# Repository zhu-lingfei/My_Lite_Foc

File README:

# 基于DRV8313的FOC驱动器

## 描述

本驱动板适用于4008/4010云台无刷电机，使用不高于16V电压。主控采用STM32F103C8T6,驱动芯片为DRV8313/AT8313，最大电流2.5A，使用低侧电流采样，驱动板集成CAN收发器，使用CAN通讯控制。

<div align="center">
    
</div>

项目参考自[B站UP主：会飞的车_S](https://www.bilibili.com/video/BV1nv4y1G73a/?spm_id_from=333.999.0.0&amp;vd_source=1aaa4eb0748d3bced4e39449a442883b)的开源项目，在硬件上做出如下修改：

1. 修改原本的母线电流采样为低侧电流采样，母线电流采样对运放要求较高，需要使用比常规放大器更好的PWM抑制功能的高精度双向运放，原设计采用INA240,价格比较高；低侧采样则对运放没什么要求，这里使用INA181。
   
   <div align="center">
    
   </div>
   <div align="center">

   </div>

2. 运放参考电压使用电阻分压加电压跟随器，降低阻抗。参考电压为1.65v，满足双向电流采样的电压偏置。可使用OPA333或OPA348，OPA348价格比较低。
   
   <div align="center">
    
   </div>

由于原本是画在一块方板子上的，后来改了圆板子，很多布局是直接复制过来的，也懒得修改了，看起来有些奇怪，但是能跑就行。
运放可以只焊接两个，即U相和V相，W相（红框内）可不焊接。

<div align="center">
    
</div>

## 程序

固件修改自[B站UP主：会飞的车_S](https://space.bilibili.com/342241148?spm_id_from=333.788.0.0)及群主：小时候可吊了。修改的内容如下：

1. 将原本定时器更新中断中使用软件触发电流采样修改为定时器通道4输出OC4REF触发AD采样，使用ADC1和ADC2注入组分别采集U相和V相的电流，使用规则组采集电源电压。
2. 添加CAN控制指令
3. 添加FreeRtos
   [GIT仓库地址](https://github.com/zhu-lingfei/My_Lite_Foc)（还未提交最终版本，修改ing）

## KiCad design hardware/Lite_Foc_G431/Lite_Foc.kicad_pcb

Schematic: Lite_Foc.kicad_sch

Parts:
C1, C2, C3, C4, C30, C31, C32, C33: 100nf; C_0603_1608Metric
C5: 0.1u; C_1206_3216Metric
C6: 320uf; CP_Elec_8x10
C7, C22: 0.1u; C_0603_1608Metric
C8, C26: 0.01u; C_0603_1608Metric
C9: 4.7uF; R_0603_1608Metric
C10, C14: 104; C_0603_1608Metric
C11: 10uF; R_0603_1608Metric
C12, C13: 1uF; C_0603_1608Metric
C15: 22uF; C_0805_2012Metric
C16, C18: 10uF; C_0603_1608Metric
C17, C20, C21: C; C_0603_1608Metric
C19, C23, C24, C25, C29: 0.1uF; C_0603_1608Metric
CN1: XT30PW-M; CONN-TH_XT30PW-M
CN2: GH1.25-2PWBPZ; CONN-SMD_GH1.25-2PWBPZ
CN3: MR30PW-F; MR30-M
D1: 1N4148WS; D_SOD-323
D4: SMAJ30CA; SMA_L4.4-W2.6-LS5.0-BI
D5: SS34; SMA_L4.3-W2.6-LS5.2-RD
D6, D7, D8, D9, D10, D11, D12, D13, D14: 1N4148WT; D_SOD-523
FPC1: KH-FG0.5-H2.0-13PIN; FPC-SMD_13P-P0.50_KINGHELM_KH-FG0.5-H2.0-13PIN
H1, H2, H3, H4: MountingHole_Pad; MountingHole_2.2mm_M2_DIN965_Pad_TopBottom
IC1: JW5026; SOT-23-6
IC2: ME6211C33M5G-N; SOT-23-5
J1: USB_C_Receptacle_USB2.0; USB_C_Receptacle_G-Switch_GT-USB-7010ASV
L1: 4.7uH; L_Changjiang_FNR4010S
L2: 15uH; L_6.3x6.3_H3
L3, L4: 0R100M; L_0603_1608Metric
Q1, Q2, Q3, Q4, Q5, Q6: AON7544
R1, R2, R3, R4, R5, R6: 2.2R; R_0603_1608Metric
R7, R8, R9: 0.01R; R_1206_3216Metric
R10, R11, R15, R16, R24: 10k; R_0603_1608Metric
R12, R28, R29, R32: R; R_0603_1608Metric
R13: 0R; R_0603_1608Metric
R14: 120R; R_0603_1608Metric
R22: 3.3R; R_0603_1608Metric
R23: 100k; R_0603_1608Metric
R25: 100K; R_0603_1608Metric
R26: 2.1K; R_0603_1608Metric
R27: 11.2K; R_0603_1608Metric
R30: 150k; R_0603_1608Metric
SW1: 按键开关-2P-3*5*2; 贴片按键-2P-3_5_2
U1: FD6288Q; QFN50P400X400X90-25N
U2: STM32G431C8Tx; LQFP-48_7x7mm_P0.5mm
U3: CH9102F; QFN-24-1EP_4x4mm_P0.5mm_EP2.6x2.6mm
U4: MP1584EN; SOIC-8_L4.9-W3.9-P1.27-LS6.0-BL-EP3.3
U5, U6, U7: INA181; SOT-23-6
U8: GH1.25-5PWBPZ; CONN-SMD_5P-P1.25_GH1.25-5PWBPZ
U9: MAX3051; SOT-23-8_L3.0-W1.7-P0.65-LS2.8-TL
Y1: Crystal_GND3; CRYSTAL-SMD_3P-L3.2-W1.3-P1.2-L

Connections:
+5V: C11.2, C12.2, C22.1, C32.2, D1.1 (K), IC2.1 (VIN), IC2.3 (CE), L1.2, R27.1, U3.7 (VDD5), U3.8 (VBUS), U9.3 (VDD)
+12V: C4.2, C9.2, C15.2, C16.2, C29.2, D12.2 (A), D13.2 (A), D14.2 (A), IC1.5 (VIN), L2.1, R25.2, R28.1, U1.4 (VCC)
/CANH: CN2.2, R14.1, U9.7 (CANH)
/CANL: CN2.1, R14.2, U9.6 (CANL)
/FDCAN_RX: U2.33 (PA11), U9.4 (RXD)
/FDCAN_TX: U2.34 (PA12), U9.1 (TXD)
/GHA: D6.1 (K), R1.1, U1.19 (HO1)
/GHB: D9.1 (K), R3.1, U1.16 (HO2)
/GHC: D11.1 (K), R5.1, U1.13 (HO3)
/GLA: D7.1 (K), R2.1, U1.11 (LO1)
/GLB: D8.1 (K), R4.1, U1.10 (LO2)
/GLC: D10.1 (K), R6.1, U1.9 (LO3)
/KEY1: R15.1, U2.39 (PA15)
/KEY2: R16.1, U2.46 (PB9)
/OSC_IN: U2.5 (PF0), Y1.1
/OSC_OUT: U2.6 (PF1), Y1.2
/SHA: C1.2, CN3.3, Q1.1 (S), Q2.3 (D), U1.18 (VS1)
/SHB: C2.2, CN3.2, Q3.1 (S), Q4.3 (D), U1.15 (VS2)
/SHC: C3.2, CN3.1, Q5.1 (S), Q6.3 (D), U1.12 (VS3)
/SPA: Q2.1 (S), R7.1, U5.3 (+)
/SPB: Q4.1 (S), R8.1, U6.3 (+)
/SPC: Q6.1 (S), R9.1, U7.3 (+)
/SPI1_MISO: U2.41 (PB4), U8.3
/SPI1_MOSI: U2.42 (PB5), U8.4
/SPI1_SCK: U2.40 (PB3), U8.2
/SWCLK: FPC1.4, U2.38 (PA14)
/SWDIO: FPC1.8, U2.37 (PA13)
/TIM1CH1: U1.22 (HIN1), U2.30 (PA8)
/TIM1CH1N: U1.1 (LIN1), U2.27 (PB13)
/TIM1CH2: U1.23 (HIN2), U2.31 (PA9)
/TIM1CH2N: U1.2 (LIN2), U2.28 (PB14)
/TIM1CH3: U1.24 (HIN3), U2.32 (PA10)
/TIM1CH3N: U1.3 (LIN3), U2.29 (PB15)
/TIM4_CH1: FPC1.1, U2.43 (PB6)
/TIM4_CH2: FPC1.2, U2.44 (PB7)
/TIM4_CH3: FPC1.3, U2.45 (PB8)
/UART1_RX: U2.25 (PB11), U3.21 (TXD)
/UART1_TX: U2.22 (PB10), U3.20 (RXD)
/USB_DN: J1.A7 (D-), J1.B7 (D-), U3.4 (D-)
/USB_DP: J1.A6 (D+), J1.B6 (D+), U3.3 (D+)
AVDD: C23.1, C24.1, C25.1, C30.2, L3.2, R10.1, U2.20 (VREF+), U2.21 (VDDA), U5.6 (V+), U6.6 (V+), U7.6 (V+)
GND: C4.1, C7.2, C9.1, C11.1, C12.1, C13.1, C14.1, C15.1, C16.1, C18.2, C19.2, C20.2, C21.2, C22.2, C23.2, C24.2, C25.2, C26.1, C29.1, C31.1, C32.1, C33.2, CN2.3, CN2.4, D5.2 (A), FPC1.13, H1.1, H2.1, H3.1, H4.1, IC1.2 (GND), IC2.2 (VSS), J1.A1 (GND), J1.A12 (GND), J1.B1 (GND), J1.B12 (GND), J1.S1 (SHIELD), L4.1, R11.2, R13.2, R24.2, R26.1, R29.2, R30.2, SW1.1, U1.6 (COM), U1.25 (EXP), U2.23 (VSS), U2.35 (VSS), U2.47 (VSS), U3.2 (GND), U3.25 (GND), U4.5 (GND), U4.9 (GND), U5.2 (GND), U6.2 (GND), U7.2 (GND), U9.2 (GND), U9.8 (RS), Y1.3
GNDA: C30.1, L4.2, U2.19 (VSSA)
GNDPWR: C5.2, C6.2, C8.2, CN1.1, D4.2 (A), R7.2, R8.2, R9.2, R13.1, U5.4 (-), U6.4 (-), U7.4 (-)
ISA: U2.8 (PA0), U5.1
ISB: U2.9 (PA1), U6.1
ISC: U2.10 (PA2), U7.1
unnamed: C8.1, R22.2
unnamed: C20.1, R12.2
unnamed: D1.2 (A), J1.A4 (VBUS), J1.A9 (VBUS), J1.B4 (VBUS), J1.B9 (VBUS)
unnamed: C17.1, D5.1 (K), L2.2, U4.1 (SW)
unnamed: D6.2 (A), Q1.2 (G), R1.2
unnamed: D7.2 (A), Q2.2 (G), R2.2
unnamed: D8.2 (A), Q4.2 (G), R4.2
unnamed: D9.2 (A), Q3.2 (G), R3.2
unnamed: D10.2 (A), Q6.2 (G), R6.2
unnamed: D11.2 (A), Q5.2 (G), R5.2
unnamed: C1.1, D12.1 (K), U1.20 (VB1)
unnamed: C2.1, D13.1 (K), U1.17 (VB2)
unnamed: C3.1, D14.1 (K), U1.14 (VB3)
unnamed: FPC1.10, R15.2
unnamed: FPC1.11, R16.2
unnamed: C10.1, IC1.1 (BST)
unnamed: IC1.4 (EN), R25.1
unnamed: IC1.3 (FB), R26.2, R27.2
unnamed: C10.2, IC1.6 (SW), L1.1
unnamed: C26.2, SW1.2, U2.7 (PG10)
unnamed: C33.1, U3.5 (VIO), U3.6 (V3)
unnamed: C17.2, U4.8 (BST)
unnamed: C21.1, R12.1, U4.3 (COMP)
unnamed: R32.1, U4.2 (EN)
unnamed: R28.2, R29.1, U4.4 (FB)
unnamed: R30.1, U4.6 (FREQ)
UDC: U2.11 (PA3)
Udc: C7.1, R23.2, R24.1
VBUS: C5.1, C6.1, C18.1, C19.1, CN1.2, D4.1 (K), Q1.3 (D), Q3.3 (D), Q5.3 (D), R22.1, R23.1, R32.2, U4.7 (VIN)
VCC_3V3: C13.2, C14.2, C31.2, FPC1.12, IC2.5 (VOUT), L3.1, U2.1 (VBAT), U2.24 (VDD), U2.36 (VDD), U2.48 (VDD)
VREF: R10.2, R11.1, U5.5 (REF), U6.5 (REF), U7.5 (REF)

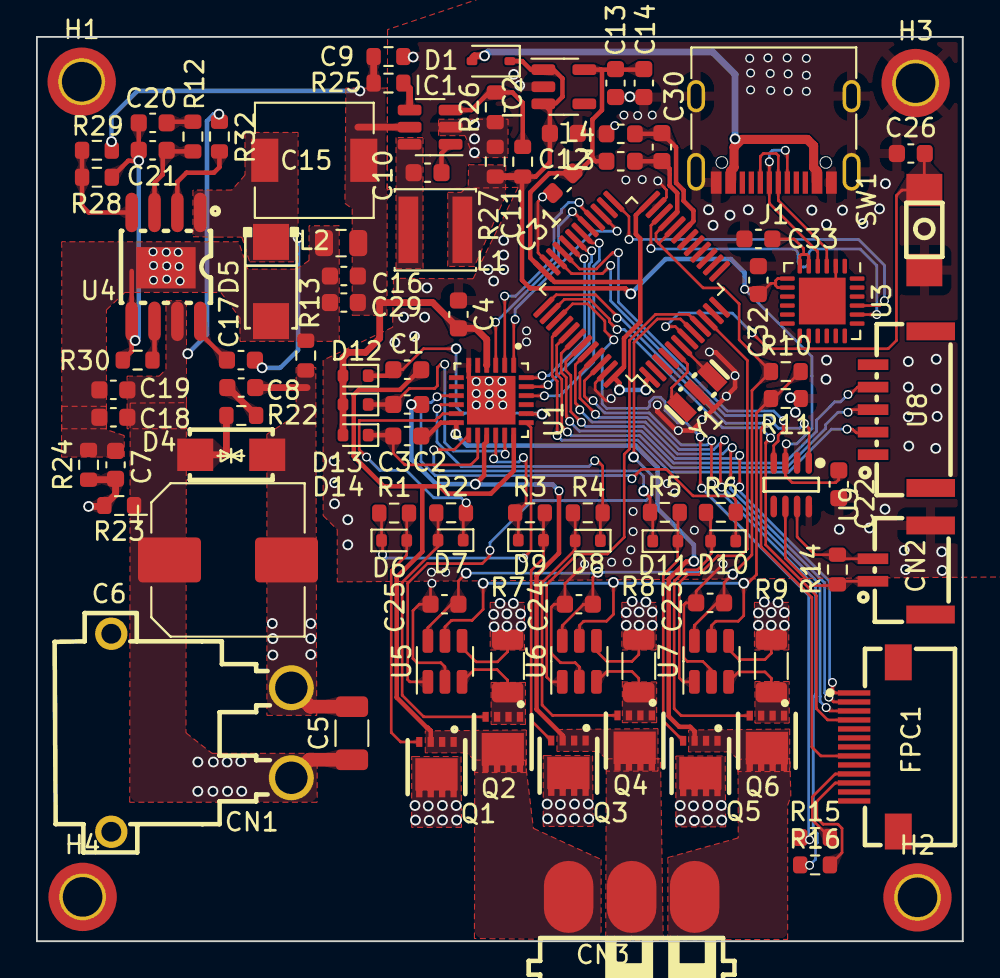
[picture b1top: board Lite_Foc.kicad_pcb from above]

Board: 2 copper layers, 51.4 x 50.2 mm, 101 parts (0 on the bottom side), 77 nets.

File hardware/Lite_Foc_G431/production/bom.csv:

Designator,Footprint,Quantity,Value,LCSC Part #
"C1, C2, C3, C30, C31, C32, C33, C4",0603,8,100nf,
"C10, C14",0603,2,104,
"C11, C16, C18",0603,3,10uF,
"C12, C13",0603,2,1uF,
C15,0805,1,22uF,
"C17, C20, C21",0603,3,C,
"C19, C23, C24, C25, C29",0603,5,0.1uF,
"C22, C7",0603,2,0.1u,
"C26, C8",0603,2,0.01u,
C5,1206,1,0.1u,
C6,CP_Elec_8x10,1,320uf,
C9,0603,1,4.7uF,
CN1,CONN-TH_XT30PW-M,1,XT30PW-M,
CN2,CONN-SMD_GH1.25-2PWBPZ,1,GH1.25-2PWBPZ,
CN3,MR30-M,1,MR30PW-F,
D1,D_SOD-323,1,1N4148WS,
"D10, D11, D12, D13, D14, D6, D7, D8, D9",D_SOD-523,9,1N4148WT,
D4,SMA_L4.4-W2.6-LS5.0-BI,1,SMAJ30CA,
D5,SMA_L4.3-W2.6-LS5.2-RD,1,SS34,
FPC1,FPC-SMD_13P-P0.50_KINGHELM_KH-FG0.5-H2.0-13PIN,1,KH-FG0.5-H2.0-13PIN,
"H1, H2, H3, H4",MountingHole_2.2mm_M2_DIN965_Pad_TopBottom,4,MountingHole_Pad,
IC1,SOT-23-6,1,JW5026,
IC2,SOT-23-5,1,ME6211C33M5G-N,
J1,USB_C_Receptacle_G-Switch_GT-USB-7010ASV,1,USB_C_Receptacle_USB2.0,
L1,L_Changjiang_FNR4010S,1,4.7uH,
L2,L_6.3x6.3_H3,1,15uH,
"L3, L4",0603,2,0R100M,
"Q1, Q2, Q3, Q4, Q5, Q6",AON7544,6,AON7544,
"R1, R2, R3, R4, R5, R6",0603,6,2.2R,
"R10, R11, R15, R16, R24",0603,5,10k,
"R12, R28, R29, R32",0603,4,R,
R13,0603,1,0R,
R14,0603,1,120R,
R22,0603,1,3.3R,
"R23, R25",0603,2,100k,
R26,0603,1,2.1K,
R27,0603,1,11.2K,
R30,0603,1,150k,
"R7, R8, R9",1206,3,0.01R,
SW1,贴片按键-2P-3_5_2,1,按键开关-2P-3*5*2,
U1,QFN50P400X400X90-25N,1,FD6288Q,
U2,LQFP-48_7x7mm_P0.5mm,1,STM32G431C8Tx,
U3,QFN-24-1EP_4x4mm_P0.5mm_EP2.6x2.6mm,1,CH9102F,
U4,SOIC-8_L4.9-W3.9-P1.27-LS6.0-BL-EP3.3,1,MP1584EN,
"U5, U6, U7",SOT-23-6,3,INA181,
U8,CONN-SMD_5P-P1.25_GH1.25-5PWBPZ,1,GH1.25-5PWBPZ,
U9,SOT-23-8_L3.0-W1.7-P0.65-LS2.8-TL,1,MAX3051,
Y1,CRYSTAL-SMD_3P-L3.2-W1.3-P1.2-L,1,Crystal_GND3,

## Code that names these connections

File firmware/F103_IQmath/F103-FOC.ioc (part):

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Mcu.Name=STM32F103C(8-B)Tx
Mcu.Package=LQFP48
Mcu.UserName=STM32F103C8Tx
PA0-WKUP.Signal=ADCx_IN0
PA10.Signal=S_TIM1_CH3
PA11.Mode=CAN_Activate
PA11.Signal=CAN_RX
PA12.Mode=CAN_Activate
PA12.Signal=CAN_TX
PA13.Mode=JTAG_5_pins
PA13.Signal=SYS_JTMS-SWDIO
PA14.Mode=JTAG_5_pins
PA14.Signal=SYS_JTCK-SWCLK
PA15.Mode=JTAG_5_pins
PA15.Signal=SYS_JTDI
PA2.Signal=ADCx_IN2
PA3.Signal=ADCx_IN3
PA4.GPIOParameters=GPIO_Speed,PinState,GPIO_Label
PA4.GPIO_Label=nRESET
PA4.GPIO_Speed=GPIO_SPEED_FREQ_LOW
PA4.PinState=GPIO_PIN_SET
PA4.Signal=GPIO_Output
PA5.Mode=Full_Duplex_Master
PA5.Signal=SPI1_SCK
PA6.Mode=Full_Duplex_Master
PA6.Signal=SPI1_MISO
PA7.Mode=Full_Duplex_Master
PA7.Signal=SPI1_MOSI
PA8.Signal=S_TIM1_CH1
PA9.Signal=S_TIM1_CH2
PB0.GPIOParameters=GPIO_Speed,PinState,GPIO_Label
PB0.GPIO_Label=SPI_CS
PB0.GPIO_Speed=GPIO_SPEED_FREQ_HIGH
PB0.PinState=GPIO_PIN_SET
PB0.Signal=GPIO_Output
PB1.GPIOParameters=GPIO_Label
PB1.GPIO_Label=nSLEEP
PB1.Signal=GPIO_Output
PB10.Mode=Asynchronous
PB10.Signal=USART3_TX
PB11.Mode=Asynchronous
PB11.Signal=USART3_RX
PB12.GPIOParameters=PinState,GPIO_Label
PB12.GPIO_Label=DRV_EN
PB12.PinState=GPIO_PIN_RESET
PB12.Signal=GPIO_Output
PB2.GPIOParameters=GPIO_Label
PB2.GPIO_Label=nFAULT
PB2.Signal=GPIO_Input
PB3.Mode=JTAG_5_pins
PB3.Signal=SYS_JTDO-TRACESWO
PB4.Mode=JTAG_5_pins
PB4.Signal=SYS_NJTRST
PB5.GPIOParameters=PinState,GPIO_Label
PB5.GPIO_Label=SYS_RLED
PB5.PinState=GPIO_PIN_SET
PB5.Signal=GPIO_Output
PB6.GPIOParameters=PinState,GPIO_Label
PB6.GPIO_Label=SYS_BLED
PB6.PinState=GPIO_PIN_SET
PB6.Signal=GPIO_Output
PB7.GPIOParameters=GPIO_Speed,PinState,GPIO_Label
PB7.GPIO_Label=Test_PIN
PB7.GPIO_Speed=GPIO_SPEED_FREQ_HIGH
PB7.PinState=GPIO_PIN_RESET
PB7.Signal=GPIO_Output
PB8.GPIOParameters=GPIO_PuPd,GPIO_Label
PB8.GPIO_Label=KEY_1
PB8.GPIO_PuPd=GPIO_PULLUP
PB8.Signal=GPIO_Input
PB9.GPIOParameters=GPIO_PuPd,GPIO_Label
PB9.GPIO_Label=KEY_2
PB9.GPIO_PuPd=GPIO_PULLUP
PB9.Signal=GPIO_Input
PD0-OSC_IN.Mode=HSE-External-Oscillator
PD0-OSC_IN.Signal=RCC_OSC_IN
PD1-OSC_OUT.Mode=HSE-External-Oscillator
PD1-OSC_OUT.Signal=RCC_OSC_OUT
RCC.SYSCLKFreq_VALUE=72000000
RCC.SYSCLKSource=RCC_SYSCLKSOURCE_PLLCLK
board=custom

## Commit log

2023-04-19 Add Project
2023-04-20 fix speed encoder bug
2023-04-20 使用cmake版本
2023-12-05 添加部分can指令
2023-12-05 remove version control
2024-05-23 添加TIM1CH4触发ADC，修改pwm为中心对齐模式2，CH4计数值改为arr-1，即CH4上升至arr-1时触发TRGO
2024-06-10 使用ADC1和ADC2注入通道分别采样一相，ADC1规则组采集母线电压，关闭扫描模式，分别添加储存函数对接到FOC计算数据，将电流采样触发方式修改为TIM1_TRGO,定时器更新中断中添加ADC注入组开启
2024-06-10 添加硬件
